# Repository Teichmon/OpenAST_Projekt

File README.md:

View this project on [CADLAB.io](https://cadlab.io/project/28691).

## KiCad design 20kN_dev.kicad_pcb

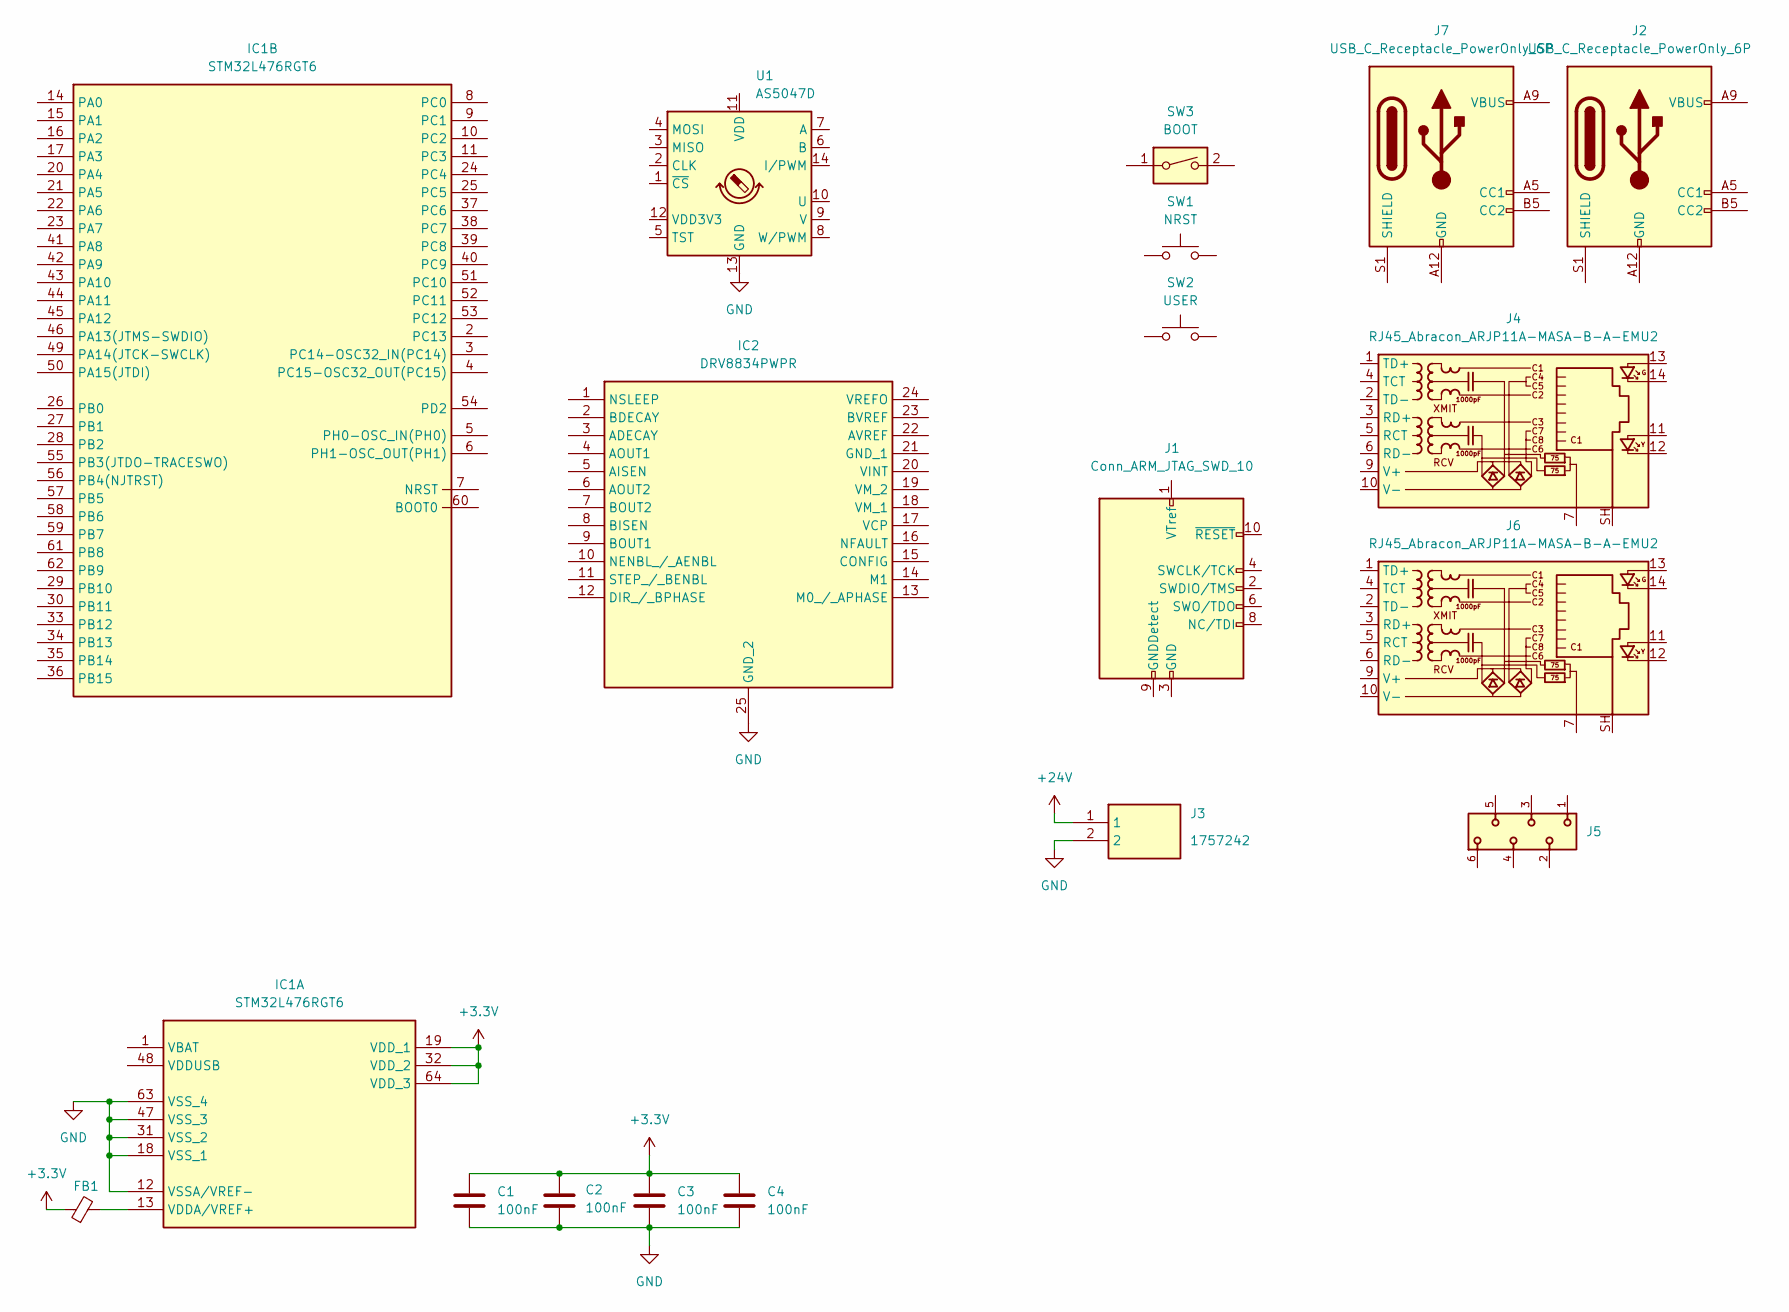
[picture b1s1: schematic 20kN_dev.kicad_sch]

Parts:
C1, C2, C3, C4: 100nF; C_0201_0603Metric
FB1: FerriteBead_Small
IC1: STM32L476RGT6; LQFP-64_10x10mm_P0.5mm; Mouser Part Number 511-STM32L476RGT6
IC2: DRV8834PWPR; HTSSOP-24-1EP_4.4x7.8mm_P0.65mm_EP3.2x5mm; Mouser Part Number 595-DRV8834PWPR
J1: Conn_ARM_JTAG_SWD_10; PinHeader_2x05_P1.27mm_Vertical_SMD
J2, J7: USB_C_Receptacle_PowerOnly_6P; USB_C_Receptacle_GCT_USB4135-GF-A_6P_TopMnt_Horizontal
J3: 1757242; 1757242_01x02_2.54mm_TH_RightAngle; Mouser Part Number 651-1757242
J4, J6: RJ45_Abracon_ARJP11A-MASA-B-A-EMU2; RJ45_Amphenol_RJHSE538X
J5: 690367180672; 690367180672_02x03_TH_MicroMatch; PART-NUMBER 690367180672
SW1: NRST; SW_Push_SPST_NO_Alps_SKRK
SW2: USER; SW_Push_SPST_NO_Alps_SKRK
SW3: BOOT; SW_DIP_SPSTx01_Slide_6.7x4.1mm_W6.73mm_P2.54mm_LowProfile_J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
U1: AS5047D; TSSOP-14_4.4x5mm_P0.65mm

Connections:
+3.3V: C1.1, C2.1, C3.1, C4.1, FB1.1, IC1.19 (VDD_1), IC1.32 (VDD_2), IC1.64 (VDD_3)
+24V: J3.1
GND: C1.2, C2.2, C3.2, C4.2, IC1.12 (VSSA/VREF-), IC1.18 (VSS_1), IC1.31 (VSS_2), IC1.47 (VSS_3), IC1.63 (VSS_4), IC2.25 (GND_2), J3.2, U1.13 (GND)
unnamed: FB1.2, IC1.13 (VDDA/VREF+)
unnamed: J1.3 (GND), J1.5 (GND)
unnamed: J2.A12 (GND), J2.B12 (GND)
unnamed: J2.A9 (VBUS), J2.B9 (VBUS)
unnamed: J7.A12 (GND), J7.B12 (GND)
unnamed: J7.A9 (VBUS), J7.B9 (VBUS)

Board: 2 copper layers, 17 parts (5 on the bottom side), 7 nets, no tracks yet.

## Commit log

2024-11-25 Initial Stage
2024-11-25 Test Stage Added Pushbutton
2024-11-25 add a Wire
2024-11-25 add GND Test
2024-11-25 Git ignore commit
2024-11-25 Test Branch Stepper Motor
2024-11-25 change Stepper Test
2024-11-25 Backlink to CADLAB.io has been added.
